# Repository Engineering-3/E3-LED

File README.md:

E3-LED
========================

This is the LED board used with the Engineering^3 curriculum and RCM Control Stack. Please see [Engineering3](http://engineering3.org/) for more information on the complete RCM Control Stack project.

Repository Contents
-------------------

* **/E3-LED_v1_3/** - Eagle schematic/board files, gerbers, and BOM

Version History
---------------
* [E3-LED_v1_3](https://github.com/Engineering-3/E3-LED/tree/master/E3-LED_v1_3)- First released version

License Information
-------------------
Hardware is released under [Solderpad Hardware License v0.51](http://solderpad.org/licenses/SHL-0.51/).
Distributed as-is; no warranty is given.

Getting Started Help
--------------------
This is a Plug-n-Play board.

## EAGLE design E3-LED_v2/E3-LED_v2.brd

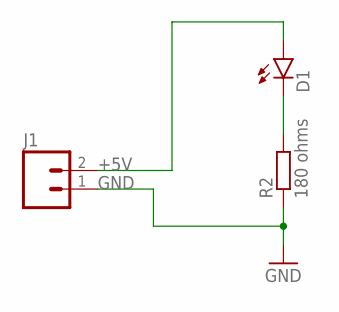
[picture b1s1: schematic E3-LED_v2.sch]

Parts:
D1: LED5MM
J1: M02PTH; 1X02
R2: 180 ohms; R0603

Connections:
+5V: D1.A, J1.2
GND: J1.1, R2.1
unnamed: D1.K (C), R2.2

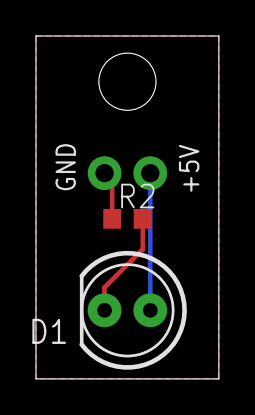
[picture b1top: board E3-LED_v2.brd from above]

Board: 2 copper layers, 10.2 x 19.1 mm, 3 parts (1 on the bottom side), 3 nets.

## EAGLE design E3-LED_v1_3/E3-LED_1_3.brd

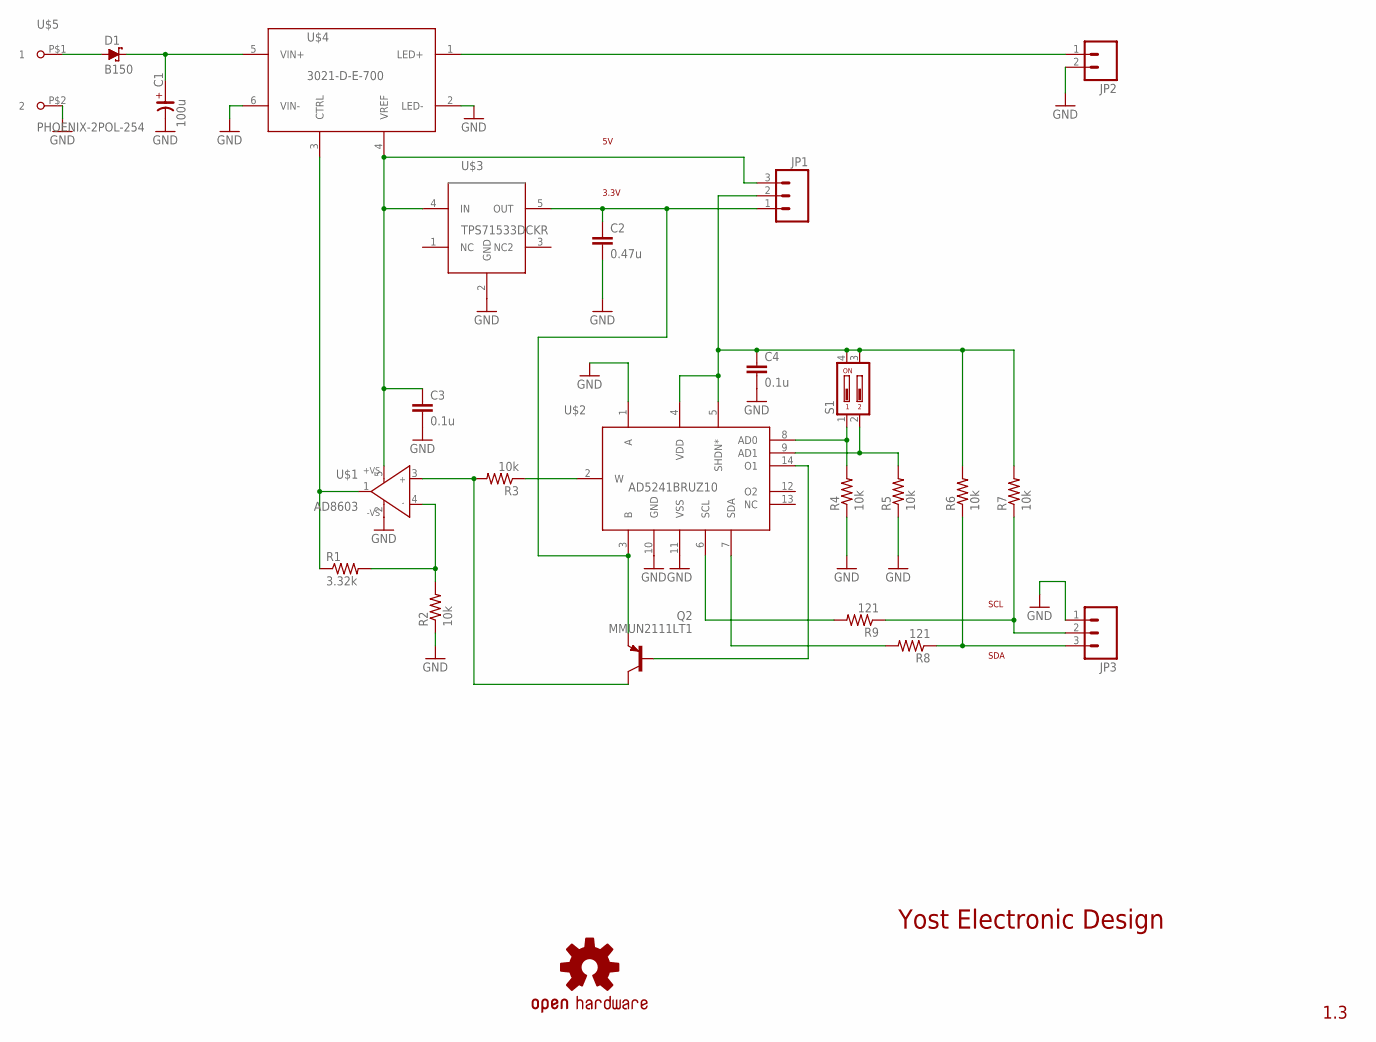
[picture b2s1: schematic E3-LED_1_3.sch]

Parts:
C1: 100u; SV-E/F
C2: 0.47u; 0805
C3, C4: 0.1u; 0805
D1: B150; SMB
JP1, JP3: M03PTH; 1X03
JP2: M02PTH; 1X02
LOGO1: OSHW-LOGOM; OSHW-LOGO-M
Q2: MMUN2111LT1; SC59-BEC
R1: 3.32k; 0805
R2, R3, R4, R5, R6, R7: 10k; 0805
R8, R9: 121; 0805
S1: SD4-02
U$1: AD8603; SOT23-5
U$2: AD5241BRUZ10; TSOT14
U$3: TPS71533DCKR; SC70-5
U$4: 3021-D-E-700
U$5: PHOENIX-2POL-254; 2-POL-254
U$6: ROHS_GARBAGE; ROHS_GARBAGE_5MM

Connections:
3.3V: C2.1, JP1.1, Q2.E, U$2.3 (B), U$3.5 (OUT)
5V: C3.1, JP1.3, U$1.5 (+VS), U$3.4 (IN), U$4.4 (VREF)
5V/3.3V: C4.1, JP1.2, R6.2, R7.2, S1.3, S1.4, U$2.4 (VDD), U$2.5 (SHDN*)
AD0: R4.2, S1.1, U$2.8 (AD0)
AD1: R5.2, S1.2, U$2.9 (AD1)
CTRL: R1.1, U$1.1 (OUT), U$4.3 (CTRL)
GND: C1.-, C2.2, C3.2, C4.2, JP2.2, JP3.1, R2.1, R4.1, R5.1, U$1.2 (-VS), U$2.1 (A), U$2.10 (GND), U$2.11 (VSS), U$3.2 (GND), U$4.2 (LED-), U$4.6 (VIN-), U$5.P$2 (2)
LED+: JP2.1, U$4.1 (LED+)
unnamed: R1.2, R2.2, U$1.4 (IN-)
unnamed: Q2.C, R3.2, U$1.3 (NUMBER)
unnamed: R3.1, U$2.2 (W)
O1: Q2.B, U$2.14 (O1)
SCL: R9.2, U$2.6 (SCL)
SCLPIN: JP3.2, R7.1, R9.1
SDA: R8.2, U$2.7 (SDA)
SDAPIN: JP3.3, R6.1, R8.1
VIN: D1.A, U$5.P$1 (1)
VINISO: C1.+, D1.C, U$4.5 (VIN+)

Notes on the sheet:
SCL
SDA
3.3V
1.3
Yost Electronic Design

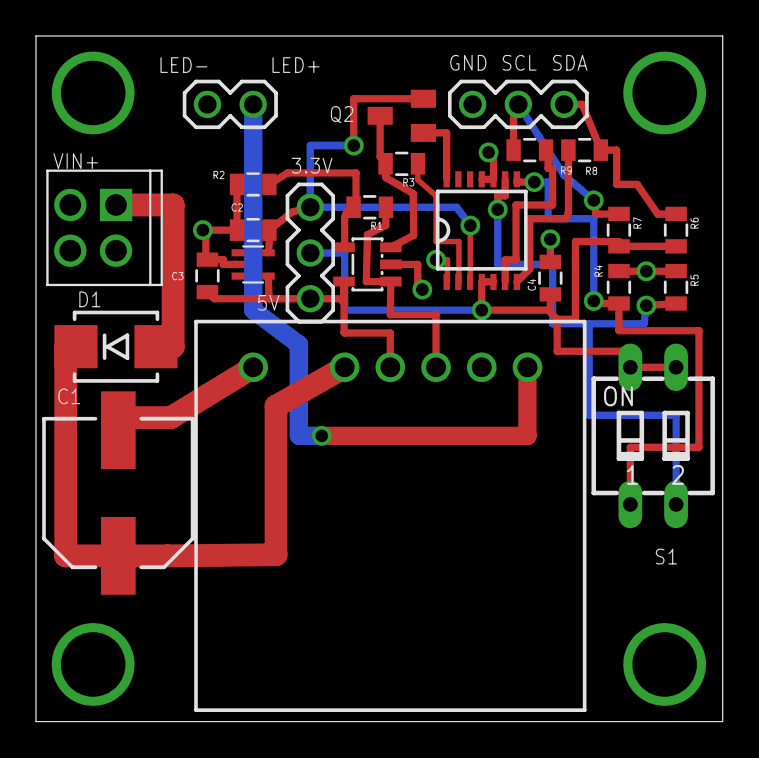
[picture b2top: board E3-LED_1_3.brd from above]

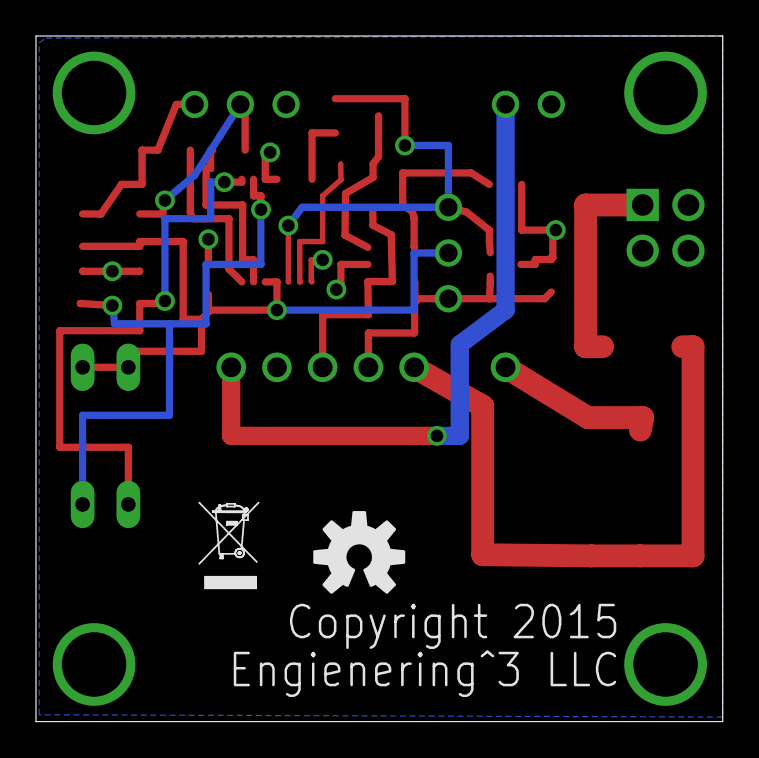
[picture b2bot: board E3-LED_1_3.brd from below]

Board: 2 copper layers, 38.2 x 38.1 mm, 26 parts (2 on the bottom side), 18 nets.

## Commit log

2015-02-18 Initial file checkin.
2015-02-18 Added BOM from Jim.
2015-02-19 Added readme file.
2015-02-19 Renamed readme.
2017-05-28 Adding v2 of the new LED board.
2017-07-14 Updated BOM and schematic of v2 board with final LED and resistor choice.
2017-08-07 Tweaked silk.
2017-08-07 Final version sent to fab.
2017-12-04 Added dimensions.
2017-12-04 Added more dimensions.

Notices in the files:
E3-LED_v1_3/E3-LED_1_3.brd:
Copyright 2015
E3-LED_v1_3/E3-LED_1_3.sch:
Copyright 2015 Engineering^3 LLC
Copyright 2015 Engineering^3 LLC Copyright and related rights are licensed under the Solderpad Hardware License,
Version 0.51 (the “License”); you may not use this file except in compliance with the License. You may obtain a copy
parts and their libraries:
SparkFun-Aesthetics: Licensing: Creative Commons ShareAlike 4.0 International - https://creativecommons.org/licenses/by-sa/4.0
